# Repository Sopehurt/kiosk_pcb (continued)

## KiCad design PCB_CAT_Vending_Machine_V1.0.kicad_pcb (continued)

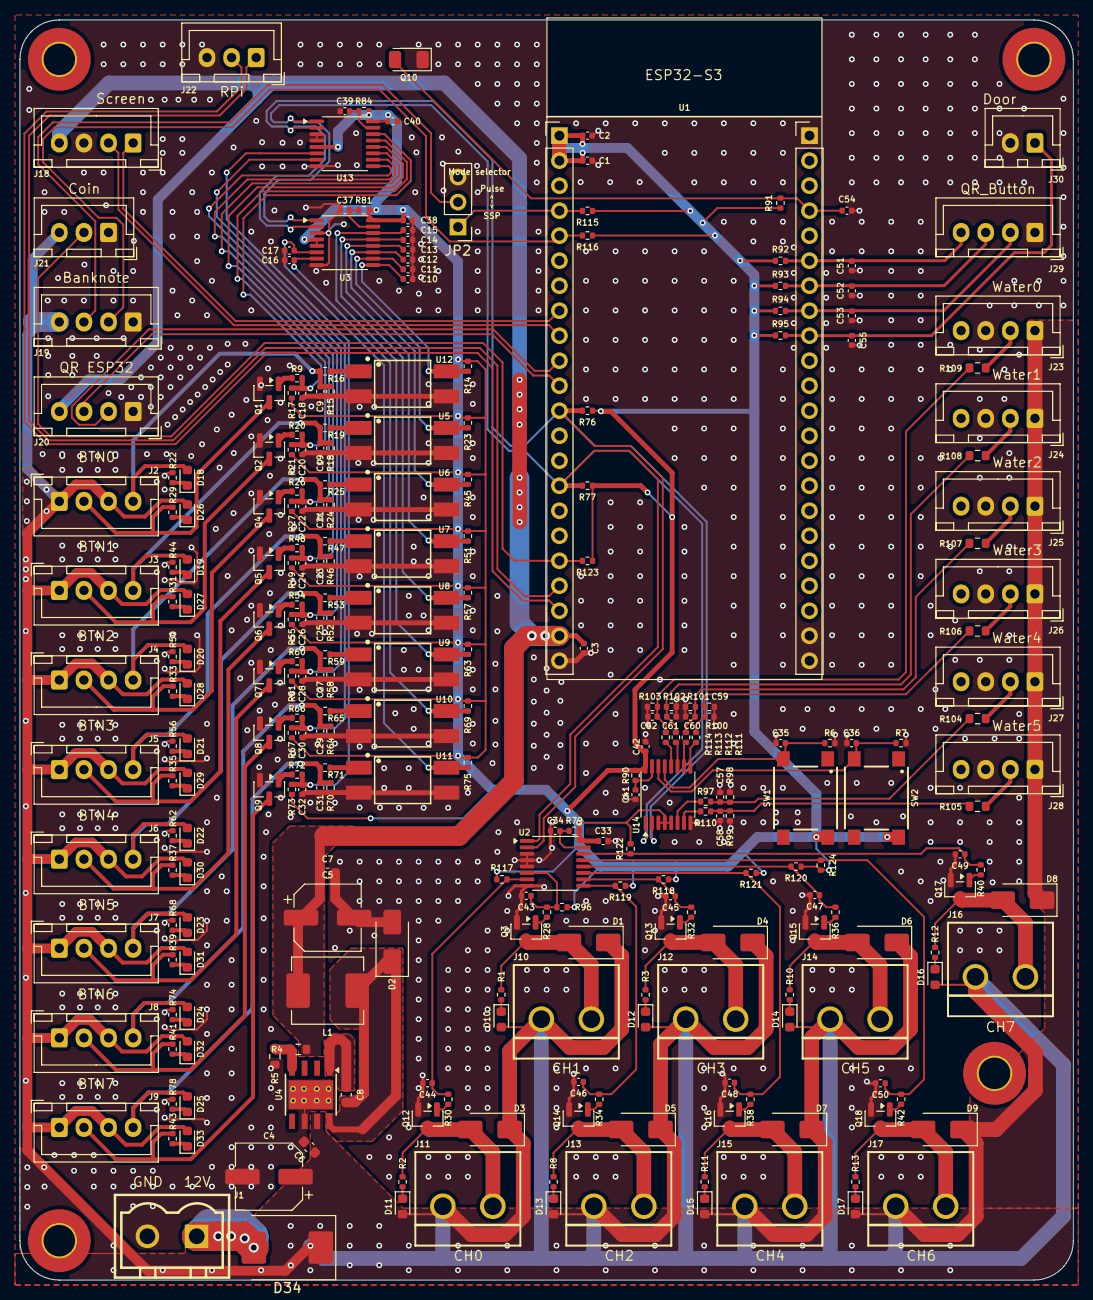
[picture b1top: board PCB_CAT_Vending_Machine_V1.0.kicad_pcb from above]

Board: 2 copper layers, 107.0 x 128.0 mm, 280 parts (0 on the bottom side), 145 nets.

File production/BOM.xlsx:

Reference | Qty | Value | Footprint | LCSC
SW1,SW2 | 2 | Button | Sharing_IC_Footprint:430182043816 | C5340127
J21,J22 | 2 | Connector 3P | Connector_JST:JST_XH_B3B-XH-A_1x03_P2.50mm_Vertical | C7429633
J10,J11,J12,J13,J14,J15,J16,J17 | 8 | Load | Sharing_Connector_Footprint:CONN-TH_CH5.08-2A | C27692
J2,J3,J4,J5,J6,J7,J8,J9,J18,J19,J20,J23,J24,J25,J26,J27,J28,J29 | 18 | Connector 4P | Connector_JST:JST_XH_B4B-XH-A_1x04_P2.50mm_Vertical | C7429634
J30 | 1 | Connector2P | Connector_JST:JST_XH_B2B-XH-A_1x02_P2.50mm_Vertical | C42441529
Q10 | 1 | PT15-21C/TR8 | LED_SMD:LED_1206_3216Metric | C41383389
D1,D3,D4,D5,D6,D7,D8,D9 | 8 | SS54 | Diode_SMD:D_SMA | C22452
D2 | 1 | SS34 | Diode_SMD:D_SMA | C8678
Q3,Q12,Q13,Q14,Q15,Q16,Q17,Q18 | 8 | AO3400A | Package_TO_SOT_SMD:SOT-23 | C20917
R4 | 1 | 15k | Resistor_SMD:R_0603_1608Metric | C22809
R5 | 1 | 4.7k | Resistor_SMD:R_0603_1608Metric | C23162
J1 | 1 | 12Vin | Sharing_Connector_Footprint:CONN-TH_2P-P5.00_XY2500V-D-5.00-2P | C505779
Q1,Q2,Q4,Q5,Q6,Q7,Q8,Q9 | 8 | 2N7002 | Package_TO_SOT_SMD:SOT-23 | C8545
D10,D11,D12,D13,D14,D15,D16,D17,D18,D19,D20,D21,D22,D23,D24,D25,D26,D27,D28,D29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 | 24 | LED | LED_SMD:LED_0603_1608Metric | C2290
U4 | 1 | TPS5430DDA | Package_SO:TI_SO-PowerPAD-8_ThermalVias | C9864
U2,U3,U13,U14 | 4 | PCA9557PW | Package_SO:TSSOP-16_4.4x5mm_P0.65mm | C141380
L1 | 1 | 33uH | Inductor_SMD:L_TechFuse_SL0650 | C5127476
U5,U6,U7,U8,U9,U10,U11,U12 | 8 | PC817C-S | Sharing_IC_Footprint:SOP-4_L6.5-W4.6-P2.54-LS10.3-TL | C3008369
C4,C5 | 2 | 220uF | Capacitor_SMD:CP_Elec_6.3x7.7 | C696188
R1,R2,R3,R8,R10,R11,R12,R13,R22,R29,R31,R33,R35,R37,R39,R41,R43,R44,R50,R56,R62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 | 24 | 1k | Resistor_SMD:R_0402_1005Metric | C11702
R6,R7,R14,R15,R17,R18,R21,R23,R24,R27,R45,R46,R49,R51,R52,R55,R57,R58,R61,R63,R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 | 49 | 10k | Resistor_SMD:R_0402_1005Metric | C25744
R9,R20,R26,R28,R30,R32,R34,R36,R38,R40,R42,R48,R54,R60,R66,R72,R97,R110,R111,R1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 | 22 | 220 | Resistor_SMD:R_0402_1005Metric | C25091
R16,R19,R25,R47,R53,R59,R65,R71 | 8 | 2.2k | Resistor_SMD:R_0402_1005Metric | C25879
R76,R77,R115,R116,R123 | 5 | 4.7k | Resistor_SMD:R_0402_1005Metric | C25900
R104,R105,R106,R107,R108,R109 | 6 | 27k | Resistor_SMD:R_0603_1608Metric | C22967
C1,C2,C3,C33,C34,C37,C38,C39,C40,C41,C42,C51,C52,C53,C55 | 15 | 100nF | Capacitor_SMD:C_0402_1005Metric | C1525
C6 | 1 | 100nF | Capacitor_SMD:C_0603_1608Metric | C14663
C7 | 1 | 10uF | Capacitor_SMD:C_0603_1608Metric | C96446
C8 | 1 | 10nF | Capacitor_SMD:C_0603_1608Metric | C57112
C9,C10,C11,C12,C13,C14,C15,C16,C17,C18,C19,C20,C21,C22,C23,C24,C25,C26,C27,C28,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 | 41 | 10nF | Capacitor_SMD:C_0402_1005Metric | C15195
P1,P2 | 2 | ZX-PM2.54-1-22PY |  | C7499337

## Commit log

2026-03-13 PCB Connector Position
2026-03-13 SCH finish
2026-03-15 finish no review
2026-03-15 success
2026-03-16 Frab1
2026-05-17 to Kicad 10
